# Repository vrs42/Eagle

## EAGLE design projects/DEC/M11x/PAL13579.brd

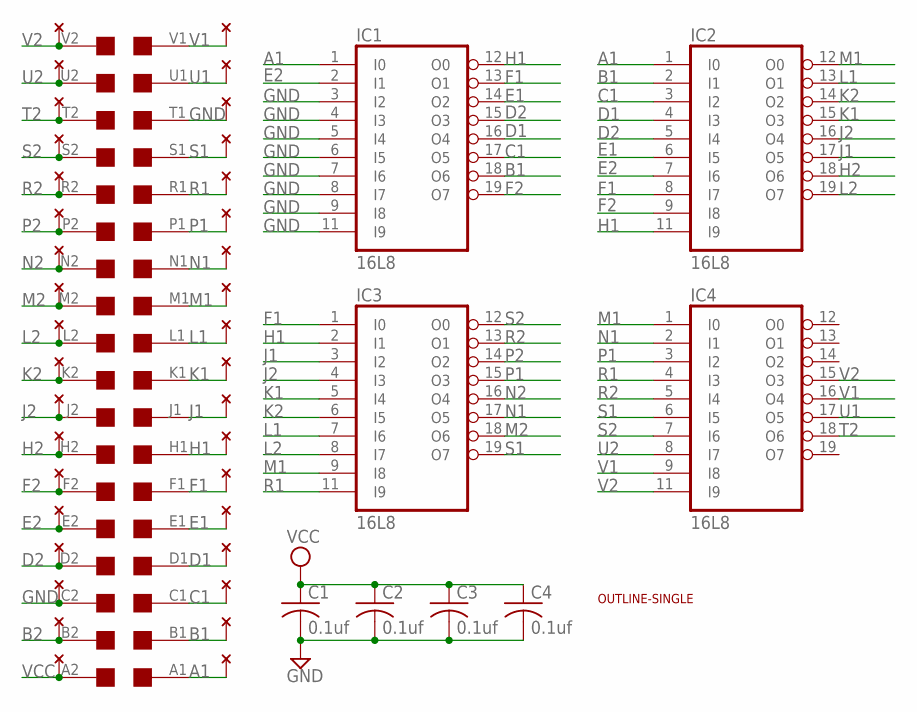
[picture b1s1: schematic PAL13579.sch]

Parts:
C1, C2, C3, C4: 0.1uf; C050-025X075
IC1, IC2, IC3, IC4: 16L8; DIL20
U$1: EDGE-2CONNECTOR; EDGE-CON2
U$2: OUTLINE-SINGLE; SINGLE
U$4: THRU-HOLE2A; THRU-HOLEA

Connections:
A1: IC1.1 (I0), IC2.1 (I0), U$1.A1, U$4.A1
B1: IC1.18 (O6), IC2.2 (I1), U$1.B1, U$4.B1
B2: U$1.B2, U$4.B2
C1: IC1.17 (O5), IC2.3 (I2), U$1.C1, U$4.C1
D1: IC1.16 (O4), IC2.4 (I3), U$1.D1, U$4.D1
D2: IC1.15 (O3), IC2.5 (I4), U$1.D2, U$4.D2
E1: IC1.14 (O2), IC2.6 (I5), U$1.E1, U$4.E1
E2: IC1.2 (I1), IC2.7 (I6), U$1.E2, U$4.E2
F1: IC1.13 (O1), IC2.8 (I7), IC3.1 (I0), U$1.F1, U$4.F1
F2: IC1.19 (O7), IC2.9 (I8), U$1.F2, U$4.F2
GND: C1.2, C2.2, C3.2, C4.2, IC1.3 (I2), IC1.4 (I3), IC1.5 (I4), IC1.6 (I5), IC1.7 (I6), IC1.8 (I7), IC1.9 (I8), IC1.10 (GND), IC1.11 (I9), IC2.10 (GND), IC3.10 (GND), IC4.10 (GND), U$1.C2, U$1.T1, U$4.C2, U$4.T1
H1: IC1.12 (O0), IC2.11 (I9), IC3.2 (I1), U$1.H1, U$4.H1
H2: IC2.18 (O6), U$1.H2, U$4.H2
J1: IC2.17 (O5), IC3.3 (I2), U$1.J1, U$4.J1
J2: IC2.16 (O4), IC3.4 (I3), U$1.J2, U$4.J2
K1: IC2.15 (O3), IC3.5 (I4), U$1.K1, U$4.K1
K2: IC2.14 (O2), IC3.6 (I5), U$1.K2, U$4.K2
L1: IC2.13 (O1), IC3.7 (I6), U$1.L1, U$4.L1
L2: IC2.19 (O7), IC3.8 (I7), U$1.L2, U$4.L2
M1: IC2.12 (O0), IC3.9 (I8), IC4.1 (I0), U$1.M1, U$4.M1
M2: IC3.18 (O6), U$1.M2, U$4.M2
N1: IC3.17 (O5), IC4.2 (I1), U$1.N1, U$4.N1
N2: IC3.16 (O4), U$1.N2, U$4.N2
P1: IC3.15 (O3), IC4.3 (I2), U$1.P1, U$4.P1
P2: IC3.14 (O2), U$1.P2, U$4.P2
R1: IC3.11 (I9), IC4.4 (I3), U$1.R1, U$4.R1
R2: IC3.13 (O1), IC4.5 (I4), U$1.R2, U$4.R2
S1: IC3.19 (O7), IC4.6 (I5), U$1.S1, U$4.S1
S2: IC3.12 (O0), IC4.7 (I6), U$1.S2, U$4.S2
T2: IC4.18 (O6), U$1.T2, U$4.T2
U1: IC4.17 (O5), U$1.U1, U$4.U1
U2: IC4.8 (I7), U$1.U2, U$4.U2
V1: IC4.9 (I8), IC4.16 (O4), U$1.V1, U$4.V1
V2: IC4.11 (I9), IC4.15 (O3), U$1.V2, U$4.V2
VCC: C1.1, C2.1, C3.1, C4.1, IC1.20 (VCC), IC2.20 (VCC), IC3.20 (VCC), IC4.20 (VCC), U$1.A2, U$4.A2

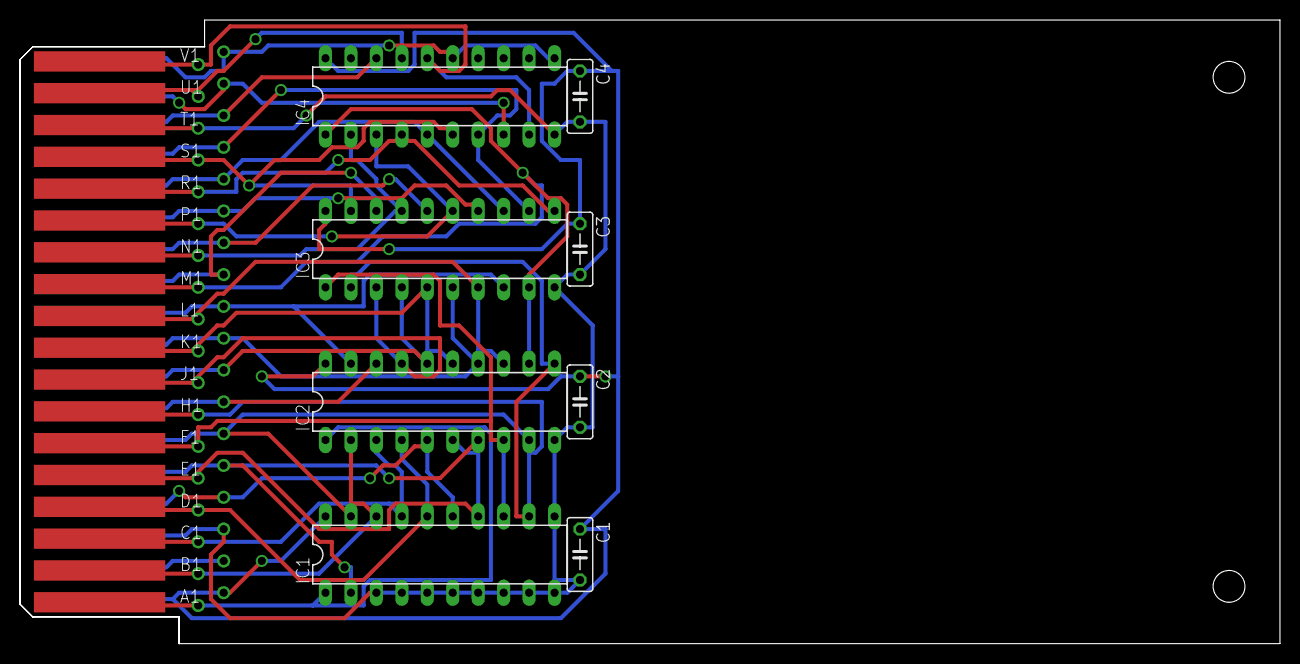
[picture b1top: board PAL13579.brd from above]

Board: 2 copper layers, 125.7 x 62.2 mm, 11 parts (0 on the bottom side), 35 nets.

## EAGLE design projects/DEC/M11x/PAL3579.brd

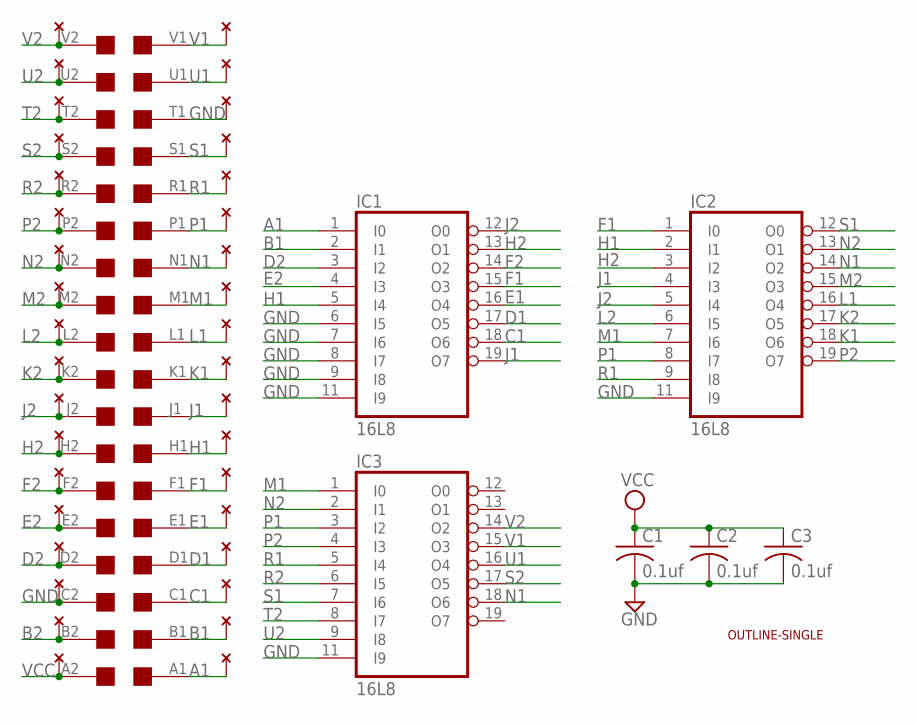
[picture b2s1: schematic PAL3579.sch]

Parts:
C1, C2, C3: 0.1uf; C050-025X075
IC1, IC2, IC3: 16L8; DIL20
U$1: EDGE-2CONNECTOR; EDGE-CON2
U$2: OUTLINE-SINGLE; SINGLE
U$4: THRU-HOLE2A; THRU-HOLEA

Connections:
A1: IC1.1 (I0), U$1.A1, U$4.A1
B1: IC1.2 (I1), U$1.B1, U$4.B1
B2: U$1.B2, U$4.B2
C1: IC1.18 (O6), U$1.C1, U$4.C1
D1: IC1.17 (O5), U$1.D1, U$4.D1
D2: IC1.3 (I2), U$1.D2, U$4.D2
E1: IC1.16 (O4), U$1.E1, U$4.E1
E2: IC1.4 (I3), U$1.E2, U$4.E2
F1: IC1.15 (O3), IC2.1 (I0), U$1.F1, U$4.F1
F2: IC1.14 (O2), U$1.F2, U$4.F2
GND: C1.2, C2.2, C3.2, IC1.6 (I5), IC1.7 (I6), IC1.8 (I7), IC1.9 (I8), IC1.10 (GND), IC1.11 (I9), IC2.10 (GND), IC2.11 (I9), IC3.10 (GND), IC3.11 (I9), U$1.C2, U$1.T1, U$4.C2, U$4.T1
H1: IC1.5 (I4), IC2.2 (I1), U$1.H1, U$4.H1
H2: IC1.13 (O1), IC2.3 (I2), U$1.H2, U$4.H2
J1: IC1.19 (O7), IC2.4 (I3), U$1.J1, U$4.J1
J2: IC1.12 (O0), IC2.5 (I4), U$1.J2, U$4.J2
K1: IC2.18 (O6), U$1.K1, U$4.K1
K2: IC2.17 (O5), U$1.K2, U$4.K2
L1: IC2.16 (O4), U$1.L1, U$4.L1
L2: IC2.6 (I5), U$1.L2, U$4.L2
M1: IC2.7 (I6), IC3.1 (I0), U$1.M1, U$4.M1
M2: IC2.15 (O3), U$1.M2, U$4.M2
N1: IC2.14 (O2), IC3.18 (O6), U$1.N1, U$4.N1
N2: IC2.13 (O1), IC3.2 (I1), U$1.N2, U$4.N2
P1: IC2.8 (I7), IC3.3 (I2), U$1.P1, U$4.P1
P2: IC2.19 (O7), IC3.4 (I3), U$1.P2, U$4.P2
R1: IC2.9 (I8), IC3.5 (I4), U$1.R1, U$4.R1
R2: IC3.6 (I5), U$1.R2, U$4.R2
S1: IC2.12 (O0), IC3.7 (I6), U$1.S1, U$4.S1
S2: IC3.17 (O5), U$1.S2, U$4.S2
T2: IC3.8 (I7), U$1.T2, U$4.T2
U1: IC3.16 (O4), U$1.U1, U$4.U1
U2: IC3.9 (I8), U$1.U2, U$4.U2
V1: IC3.15 (O3), U$1.V1, U$4.V1
V2: IC3.14 (O2), U$1.V2, U$4.V2
VCC: C1.1, C2.1, C3.1, IC1.20 (VCC), IC2.20 (VCC), IC3.20 (VCC), U$1.A2, U$4.A2

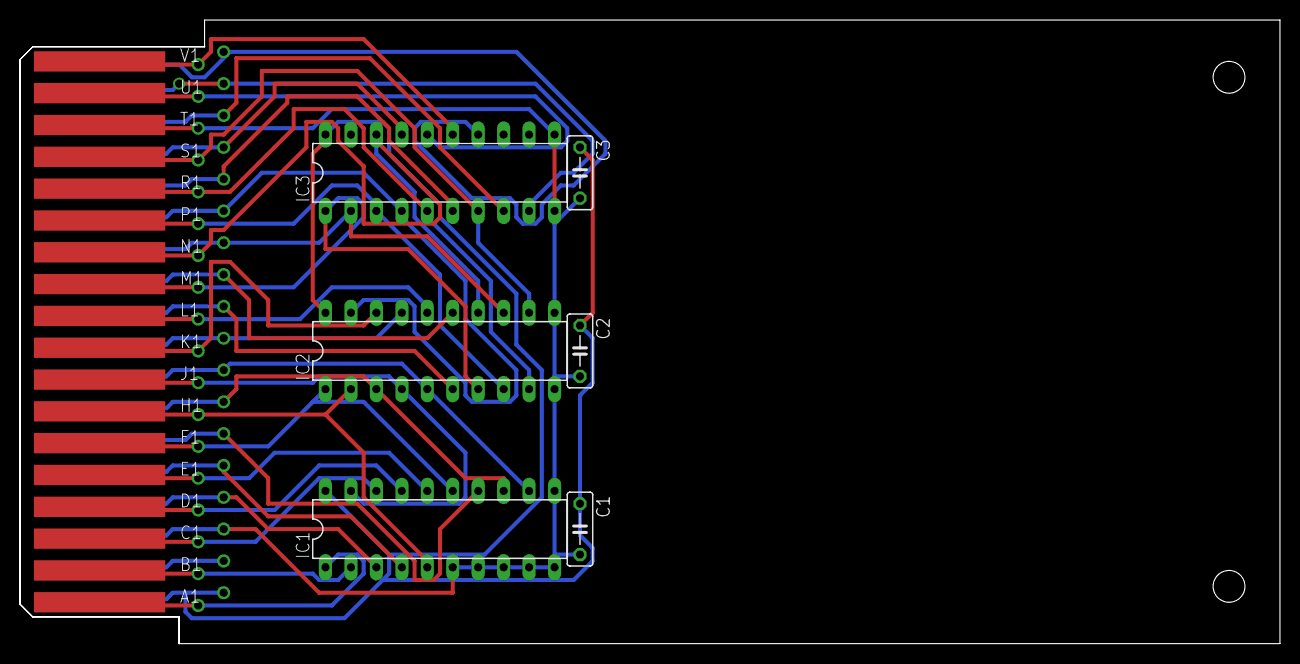
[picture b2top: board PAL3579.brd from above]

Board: 2 copper layers, 125.7 x 62.2 mm, 9 parts (0 on the bottom side), 35 nets.

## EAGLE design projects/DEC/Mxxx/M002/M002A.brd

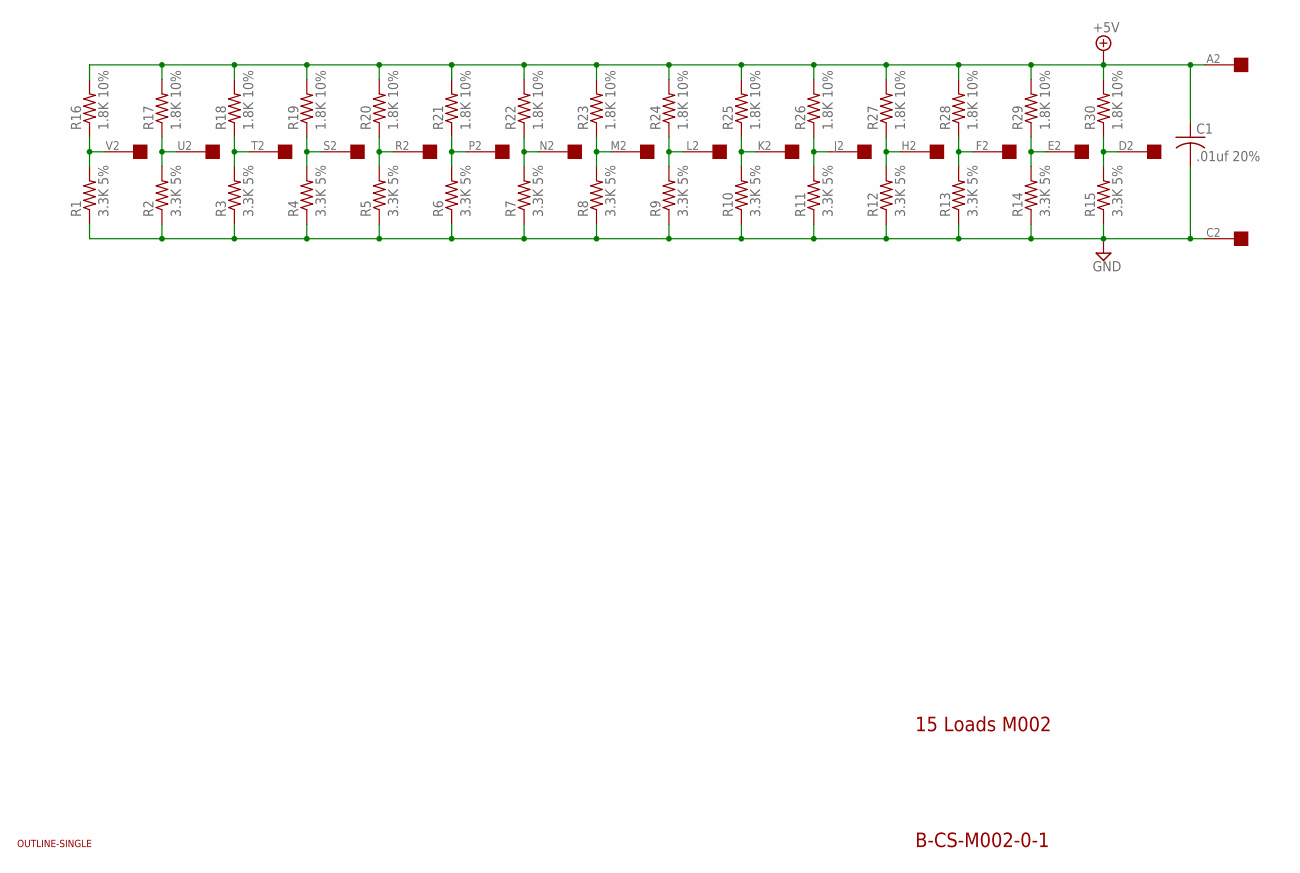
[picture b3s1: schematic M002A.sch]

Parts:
C1: .01uf 20%; C050-025X075
R1, R2, R3, R4, R5, R6, R7, R8, R9, R10, R11, R12, R13, R14, R15: 3.3K 5%; 0207/10
R16, R17, R18, R19, R20, R21, R22, R23, R24, R25, R26, R27, R28, R29, R30: 1.8K 10%; 0207/10
U$1: OUTLINE-SINGLE; SINGLE
U$2: EDGE-1; EDGE-CON1

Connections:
+5V: C1.1, R16.2, R17.2, R18.2, R19.2, R20.2, R21.2, R22.2, R23.2, R24.2, R25.2, R26.2, R27.2, R28.2, R29.2, R30.2, U$2.A2
GND: C1.2, R1.1, R2.1, R3.1, R4.1, R5.1, R6.1, R7.1, R8.1, R9.1, R10.1, R11.1, R12.1, R13.1, R14.1, R15.1, U$2.C2
unnamed: R1.2, R16.1, U$2.V2
unnamed: R2.2, R17.1, U$2.U2
unnamed: R3.2, R18.1, U$2.T2
unnamed: R4.2, R19.1, U$2.S2
unnamed: R5.2, R20.1, U$2.R2
unnamed: R6.2, R21.1, U$2.P2
unnamed: R7.2, R22.1, U$2.N2
unnamed: R8.2, R23.1, U$2.M2
unnamed: R9.2, R24.1, U$2.L2
unnamed: R10.2, R25.1, U$2.K2
unnamed: R11.2, R26.1, U$2.J2
unnamed: R12.2, R27.1, U$2.H2
unnamed: R13.2, R28.1, U$2.F2
unnamed: R15.2, R30.1, U$2.D2
unnamed: R14.2, R29.1, U$2.E2

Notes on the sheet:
15 Loads M002
B-CS-M002-0-1

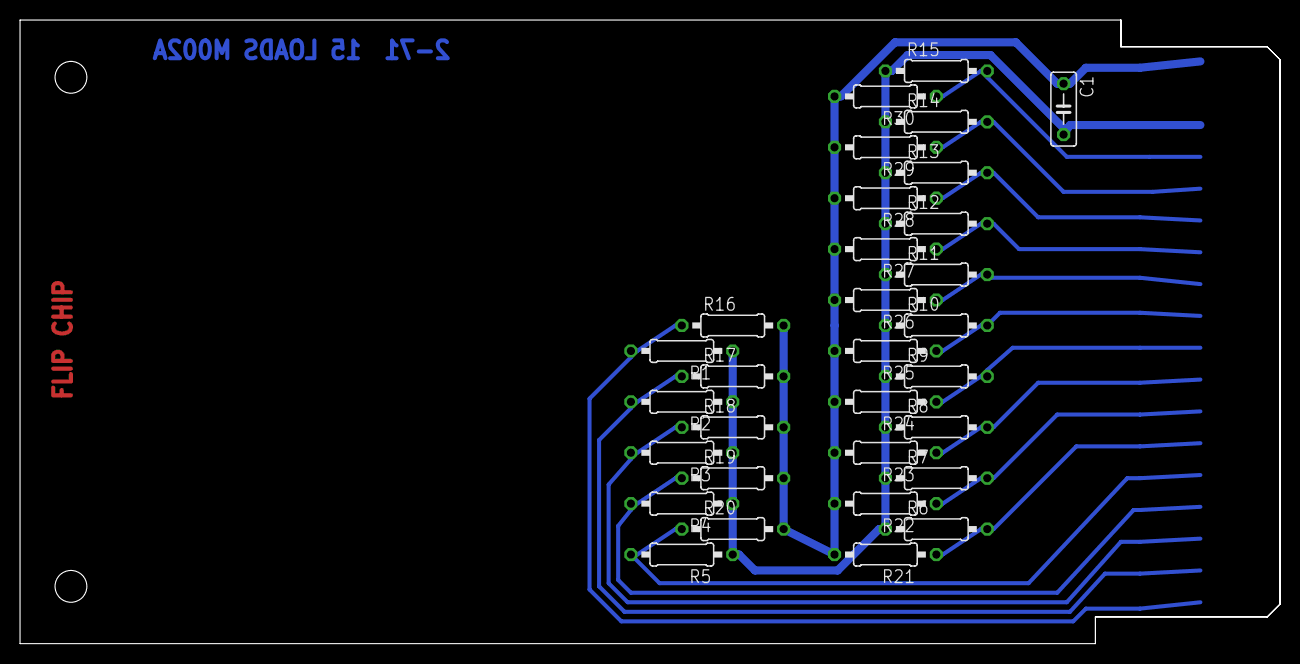
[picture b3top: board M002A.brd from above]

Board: 2 copper layers, 125.7 x 62.2 mm, 33 parts (0 on the bottom side), 17 nets.

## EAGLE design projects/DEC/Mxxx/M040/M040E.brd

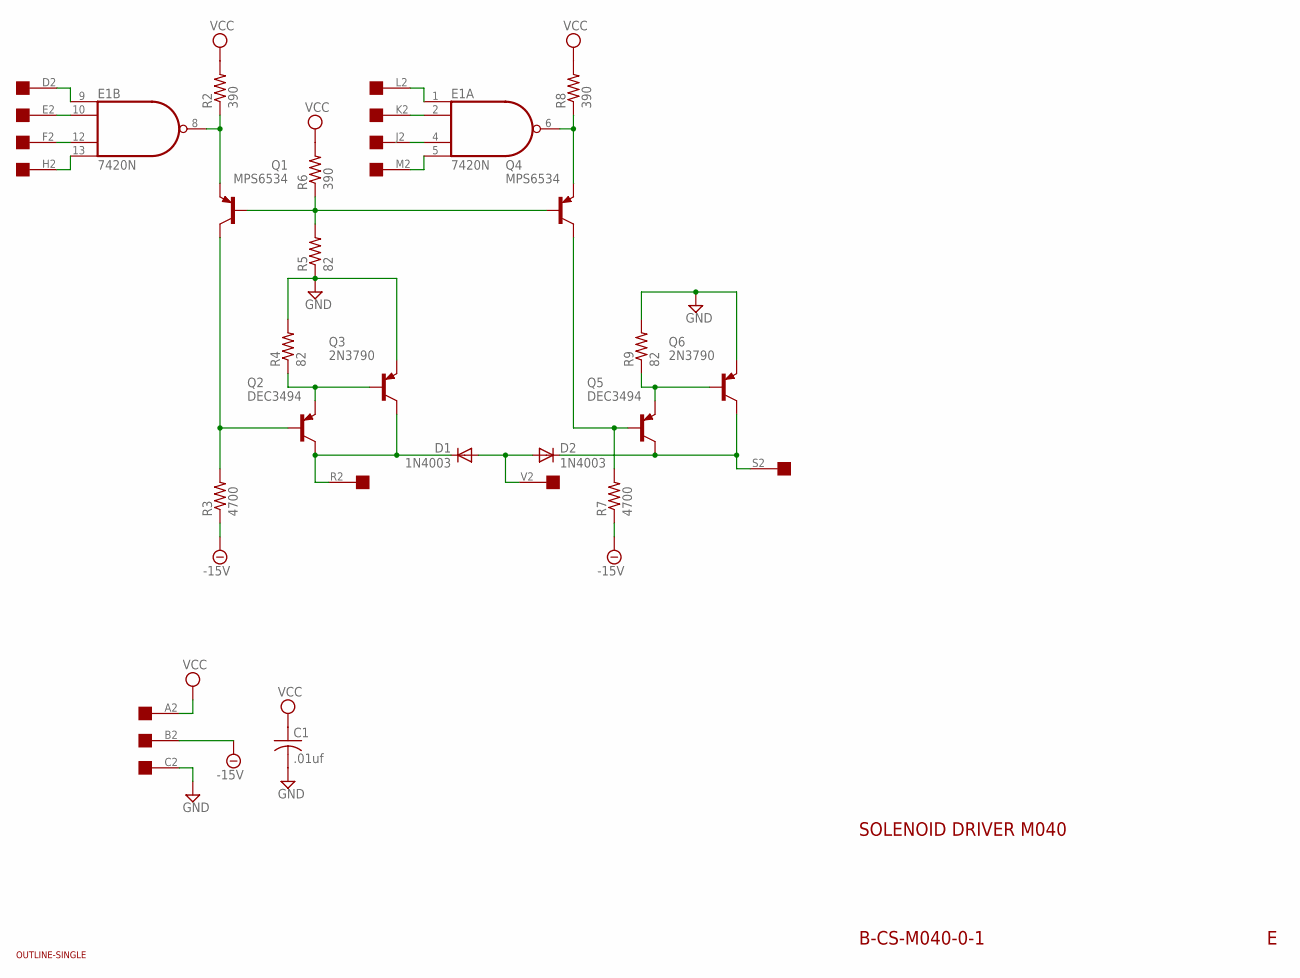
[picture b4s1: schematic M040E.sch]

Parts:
C1: .01uf; C050-025X075
D1, D2: 1N4003; DO41-10
E1: 7420N; DIL14
Q1, Q4: MPS6534; TO39
Q2, Q5: DEC3494; TO39
Q3, Q6: 2N3790; TO3
R2, R6, R8: 390; 0207/10
R3, R7: 4700; 0207/10
R4, R5, R9: 82; 0207/10
U$1: OUTLINE-SINGLE; SINGLE
U$2: EDGE-1; EDGE-CON1

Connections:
-15V: R3.1, R7.1, U$2.B2
GND: C1.2, E1.7 (GND), Q3.E, Q6.E, R4.2, R5.1, R9.2, U$2.C2
unnamed: E1.10 (I1), U$2.E2
unnamed: E1.12 (I2), U$2.F2
unnamed: E1.13 (I3), U$2.H2
unnamed: E1.9 (I0), U$2.D2
unnamed: E1.1 (I0), U$2.L2
unnamed: E1.2 (I1), U$2.K2
unnamed: E1.4 (I2), U$2.J2
unnamed: E1.5 (I3), U$2.M2
unnamed: E1.8 (O), Q1.1 (E), R2.1
unnamed: Q1.2 (B), Q4.2 (B), R5.2, R6.1
unnamed: E1.6 (O), Q4.1 (E), R8.1
unnamed: Q1.3 (C), Q2.2 (B), R3.2
unnamed: Q4.3 (C), Q5.2 (B), R7.2
unnamed: Q2.1 (E), Q3.B, R4.1
unnamed: D1.C, Q2.3 (C), Q3.C, U$2.R2
unnamed: Q5.1 (E), Q6.B, R9.1
unnamed: D2.C, Q5.3 (C), Q6.C, U$2.S2
unnamed: D1.A, D2.A, U$2.V2
VCC: C1.1, E1.14 (VCC), R2.2, R6.2, R8.2, U$2.A2

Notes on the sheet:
SOLENOID DRIVER M040
B-CS-M040-0-1

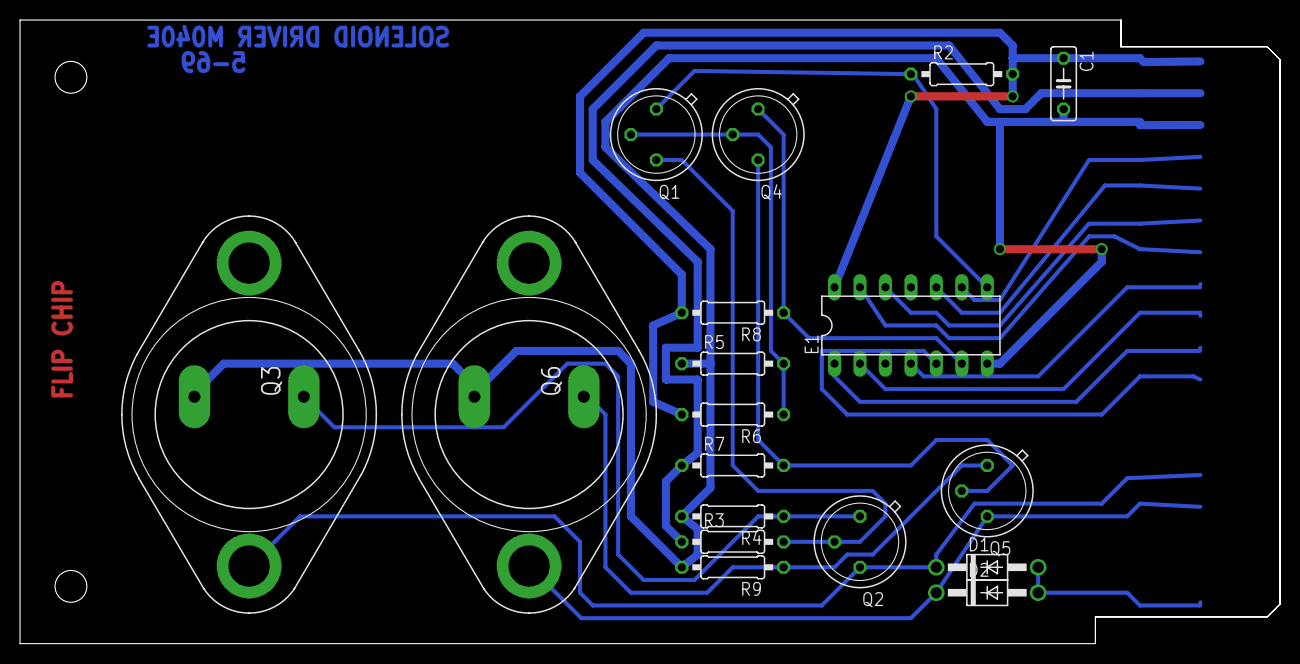
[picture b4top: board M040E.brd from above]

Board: 2 copper layers, 125.7 x 62.2 mm, 20 parts (0 on the bottom side), 21 nets.
